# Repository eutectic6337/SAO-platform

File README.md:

# SAO-platform
a minimal SAO for the less-electronic-inclined to customise 

board 37mm wide, 35mm tall

16 LED mounting points, equally spaced on a 10mm grid centered on the board

pads for 1206 surface-mount LEDs, allowing forward- or reverse-mounted LEDs

SAO plug centered on the board 

CH32V003 microcontroller with 8 PWM outputs and 8 GPIOs to control LEDs,
programmable via Single-Wire-Debug connection

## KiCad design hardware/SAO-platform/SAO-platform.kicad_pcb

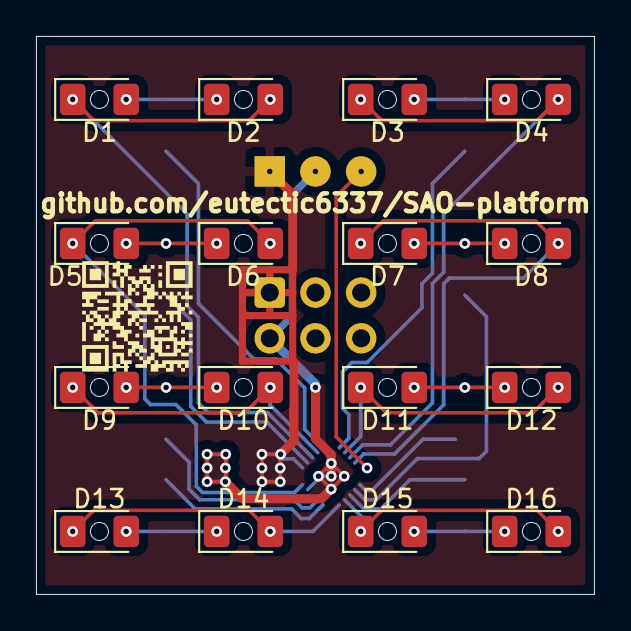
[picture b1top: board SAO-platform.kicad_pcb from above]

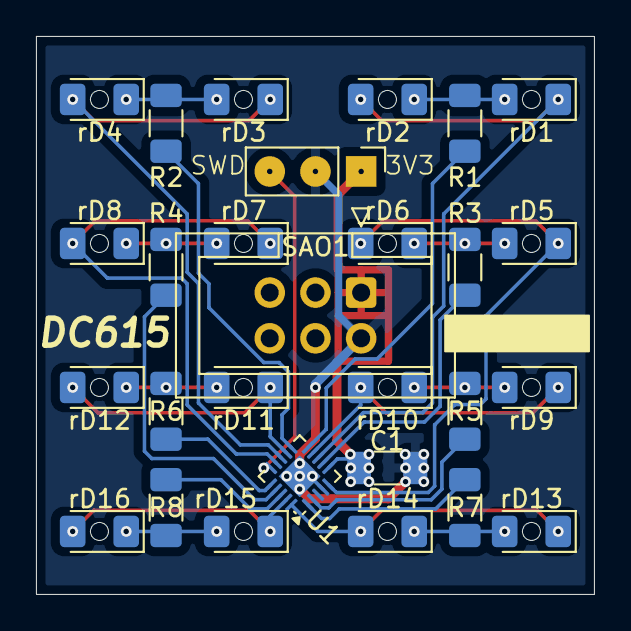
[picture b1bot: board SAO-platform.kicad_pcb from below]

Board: 2 copper layers, 31.0 x 31.0 mm, 60 parts (28 on the bottom side), 27 nets.

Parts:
C1: 100uF; C_1206_3216Metric_Pad1.33x1.80mm_HandSolder
D1, D2, D3, D4, D5, D6, D7, D8, D9, D10, D11, D12, D13, D14, D15, D16: LED; LED_1206_3216Metric_Pad1.42x1.75mm_HandSolder
PROG1: Conn_01x03; PinHeader_1x03_P2.54mm_Vertical
R1, R2, R3, R4, R5, R6, R7, R8: 47R; R_1206_3216Metric_Pad1.30x1.75mm_HandSolder
SAO1: SAO v1.69bis addon; IDC-Header_2x03_P2.54mm_Vertical
U1: WCH CH32V003F4U6; QFN-20-1EP_3x3mm_P0.4mm_EP1.65x1.65mm
h1, h2, h3, h4, h5, h6, h7, h8, h9, h10, h11, h12, h13, h14, h15, h16: (no value)
rD1, rD2, rD3, rD4, rD5, rD6, rD7, rD8, rD9, rD10, rD11, rD12, rD13, rD14, rD15, rD16: LED; LED_1206_3216Metric_Pad1.42x1.75mm_HandSolder

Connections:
+3V0: C1.1, PROG1.1, SAO1.1 (3V3), U1.6 (VDD)
/SWIO: PROG1.3, U1.15 (SWIO)
GND: C1.2, PROG1.2, SAO1.2 (GND), U1.4 (VSS), U1.21 (VSS)
GP1: D1.1 (K), D2.2 (A), U1.8 (PC1), rD1.1 (K), rD2.2 (A)
GP2: D3.1 (K), D4.2 (A), U1.13 (PC6), rD3.1 (K), rD4.2 (A)
GP3: D5.1 (K), D6.2 (A), U1.5 (PD0), rD5.1 (K), rD6.2 (A)
GP4: D7.1 (K), D8.2 (A), U1.14 (PC7), rD7.1 (K), rD8.2 (A)
GP5: D9.1 (K), D10.2 (A), U1.9 (PC2), rD9.1 (K), rD10.2 (A)
GP6: D11.1 (K), D12.2 (A), U1.12 (PC5), rD11.1 (K), rD12.2 (A)
GP7: D13.1 (K), D14.2 (A), U1.20 (PD6), rD13.1 (K), rD14.2 (A)
GP8: D15.1 (K), D16.2 (A), U1.19 (PD5), rD15.1 (K), rD16.2 (A)
unnamed: D1.2 (A), D2.1 (K), R1.2, rD1.2 (A), rD2.1 (K)
unnamed: D3.2 (A), D4.1 (K), R2.2, rD3.2 (A), rD4.1 (K)
unnamed: D5.2 (A), D6.1 (K), R3.2, rD5.2 (A), rD6.1 (K)
unnamed: D7.2 (A), D8.1 (K), R4.2, rD7.2 (A), rD8.1 (K)
unnamed: D9.2 (A), D10.1 (K), R5.2, rD9.2 (A), rD10.1 (K)
unnamed: D11.2 (A), D12.1 (K), R6.2, rD11.2 (A), rD12.1 (K)
unnamed: D13.2 (A), D14.1 (K), R7.2, rD13.2 (A), rD14.1 (K)
unnamed: D15.2 (A), D16.1 (K), R8.2, rD15.2 (A), rD16.1 (K)
PWM1: R1.1, U1.10 (TIM1_CH3)
PWM2: R2.1, U1.11 (TIM1_CH4)
PWM3: R3.1, U1.7 (TIM2_CH3)
PWM4: R4.1, U1.17 (TIM2_CH2)
PWM5: R5.1, U1.2 (TIM1_CH2)
PWM6: R6.1, U1.16 (TIM1_CH1)
PWM7: R7.1, U1.1 (TIM2_CH4)
PWM8: R8.1, U1.18 (TIM2_CH1)

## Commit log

2025-03-18 generate QR code for repo address
2025-03-18 first cut: dupe of coin, but with 1206 SMD parts
2025-03-20 layout complete, passes DRC
2025-03-20 placed silk inc. repo QR; extended ground
2025-03-20 tweak edge cuts to make size "nice"
2025-03-20 added detail to README
2025-04-16 reduce hole size on debug pads
2025-04-16 shrink the board
2025-05-12 shrunk to 8mm grid for LED centres
